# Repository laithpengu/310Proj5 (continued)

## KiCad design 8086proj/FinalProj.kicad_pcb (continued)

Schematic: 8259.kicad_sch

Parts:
C801, C802: .1uF; CP_Elec_3x5.3
J801: Conn_01x04_Male; PinHeader_1x04_P1.00mm_Vertical
R801, R802: 10k; R_0201_0603Metric
SW801: SW_Push; SW_Cherry_MX_1.00u_PCB
U801, U802: 74LS21; DIP-14_W10.16mm
U803: PAL16L8; DIP-20_W7.62mm
U804: 8259; DIP-28_W15.24mm

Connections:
/8086/INTR: U804.17 (INT); also elsewhere on the board
/8254/C2out: U804.19 (IR1); also elsewhere on the board
/8259/8279 IRQ: U804.20 (IR2); also elsewhere on the board
/16550/A0: U803.2 (I2); also elsewhere on the board
/16550/A1: U804.27 (A0); also elsewhere on the board
/16550/A2: U803.3 (I3); also elsewhere on the board
/16550/A3: U803.4 (I4); also elsewhere on the board
/16550/A4: U801.1; also elsewhere on the board
/16550/A5: U801.2; also elsewhere on the board
/16550/A6: U801.4; also elsewhere on the board
/16550/A7: U801.5; also elsewhere on the board
/16550/A8: U801.9; also elsewhere on the board
/16550/A9: U801.10; also elsewhere on the board
/16550/A10: U801.12; also elsewhere on the board
/16550/A11: U801.13; also elsewhere on the board
/16550/A12: U802.9; also elsewhere on the board
/16550/A13: U802.10; also elsewhere on the board
/16550/A14: U802.12; also elsewhere on the board
/16550/A15: U802.13; also elsewhere on the board
/16550/D0: U804.11 (D0); also elsewhere on the board
/16550/D1: U804.10 (D1); also elsewhere on the board
/16550/D2: U804.9 (D2); also elsewhere on the board
/16550/D3: U804.8 (D3); also elsewhere on the board
/16550/D4: U804.7 (D4); also elsewhere on the board
/16550/D5: U804.6 (D5); also elsewhere on the board
/16550/D6: U804.5 (D6); also elsewhere on the board
/16550/D7: U804.4 (D7); also elsewhere on the board
/16550/INTR: U804.21 (IR3); also elsewhere on the board
/16550/M/_IO: U803.1 (I1); also elsewhere on the board
/16550/_RD: U804.3 (~RD); also elsewhere on the board
/16550/_WR: U804.2 (~WR); also elsewhere on the board
unnamed: J801.1, U804.22 (IR4)
unnamed: J801.2, U804.23 (IR5)
unnamed: J801.3, U804.24 (IR6)
unnamed: J801.4, U804.25 (IR7)
unnamed: R801.1, U804.16 (~SP/~EN)
unnamed: R802.1, SW801.1, U804.18 (IR0)
unnamed: U801.6, U803.5 (I5)
unnamed: U801.8, U803.6 (I6)
unnamed: U802.8, U803.7 (I7)
unnamed: U803.19 (IO1), U804.1 (~CS)

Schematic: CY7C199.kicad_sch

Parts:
C501, C502, C503, C504, C505: .1uF; CP_Elec_3x5.3
U501: PAL16L8; DIP-20_W7.62mm
U502, U503, U504, U505: CY7C199; DIP-28_W15.24mm

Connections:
/16550/A0: U502.21 (A0), U503.21 (A0), U504.21 (A0), U505.21 (A0); also elsewhere on the board
/16550/A1: U502.23 (A1), U503.23 (A1), U504.23 (A1), U505.23 (A1); also elsewhere on the board
/16550/A2: U502.24 (A2), U503.24 (A2), U504.24 (A2), U505.24 (A2); also elsewhere on the board
/16550/A3: U502.25 (A3), U503.25 (A3), U504.25 (A3), U505.25 (A3); also elsewhere on the board
/16550/A4: U502.26 (A4), U503.26 (A4), U504.26 (A4), U505.26 (A4); also elsewhere on the board
/16550/A5: U502.1 (A5), U503.1 (A5), U504.1 (A5), U505.1 (A5); also elsewhere on the board
/16550/A6: U502.2 (A6), U503.2 (A6), U504.2 (A6), U505.2 (A6); also elsewhere on the board
/16550/A7: U502.3 (A7), U503.3 (A7), U504.3 (A7), U505.3 (A7); also elsewhere on the board
/16550/A8: U502.4 (A8), U503.4 (A8), U504.4 (A8), U505.4 (A8); also elsewhere on the board
/16550/A9: U502.5 (A9), U503.5 (A9), U504.5 (A9), U505.5 (A9); also elsewhere on the board
/16550/A10: U502.6 (A10), U503.6 (A10), U504.6 (A10), U505.6 (A10); also elsewhere on the board
/16550/A11: U502.7 (A11), U503.7 (A11), U504.7 (A11), U505.7 (A11); also elsewhere on the board
/16550/A12: U502.8 (A12), U503.8 (A12), U504.8 (A12), U505.8 (A12); also elsewhere on the board
/16550/A13: U502.9 (A13), U503.9 (A13), U504.9 (A13), U505.9 (A13); also elsewhere on the board
/16550/A14: U502.10 (A14), U503.10 (A14), U504.10 (A14), U505.10 (A14); also elsewhere on the board
/16550/D0: U502.11 (D0), U504.11 (D0); also elsewhere on the board
/16550/D1: U502.12 (D1), U504.12 (D1); also elsewhere on the board
/16550/D2: U502.13 (D2), U504.13 (D2); also elsewhere on the board
/16550/D3: U502.15 (D3), U504.15 (D3); also elsewhere on the board
/16550/D4: U502.16 (D4), U504.16 (D4); also elsewhere on the board
/16550/D5: U502.17 (D5), U504.17 (D5); also elsewhere on the board
/16550/D6: U502.18 (D6), U504.18 (D6); also elsewhere on the board
/16550/D7: U502.19 (D7), U504.19 (D7); also elsewhere on the board
/16550/D8: U503.11 (D0), U505.11 (D0); also elsewhere on the board
/16550/D9: U503.12 (D1), U505.12 (D1); also elsewhere on the board
/16550/D10: U503.13 (D2), U505.13 (D2); also elsewhere on the board
/16550/D11: U503.15 (D3), U505.15 (D3); also elsewhere on the board
/16550/D12: U503.16 (D4), U505.16 (D4); also elsewhere on the board
/16550/D13: U503.17 (D5), U505.17 (D5); also elsewhere on the board
/16550/D14: U503.18 (D6), U505.18 (D6); also elsewhere on the board
/16550/D15: U503.19 (D7), U505.19 (D7); also elsewhere on the board
/16550/M/_IO: U501.2 (I2); also elsewhere on the board
/16550/_RD: U502.27 (~WE), U503.27 (~WE), U504.27 (~WE), U505.27 (~WE); also elsewhere on the board
/16550/_WR: U502.22 (~OE), U503.22 (~OE), U504.22 (~OE), U505.22 (~OE); also elsewhere on the board
/CY7C199/A16: U501.1 (I1)
/CY7C199/_CE0: U501.19 (IO1), U502.20 (~CE), U503.20 (~CE)
/CY7C199/_CE1: U501.18 (IO2), U504.20 (~CE), U505.20 (~CE)

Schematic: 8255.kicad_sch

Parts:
C601, C602, C603: .1uf; CP_Elec_3x5.3
J601, J602, J603, J604, J605, J606, J607, J608, J609: Conn_01x08_Male; PinHeader_1x08_P1.00mm_Vertical
SW601: SW_DIP_x08; SW_DIP_SPSTx08_Slide_6.7x21.88mm_W6.73mm_P2.54mm_LowProfile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
U601: PAL16L8; DIP-20_W7.62mm
U602, U605, U608: 8255; DIP-40_W15.24mm
U603, U609: 74AUC2G32; DIP-14_W10.16mm
U604: 4011; DIP-14_W10.16mm
U606: 74AHCT04; DIP-14_W10.16mm
U607: 74LVC1G332; DIP-14_W10.16mm

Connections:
/8086/INTR: U606.1, U607.4; also elsewhere on the board
/8255/O5: U601.15 (IO5), U602.6 (~CS)
/8255/O6: U601.14 (IO6), U605.6 (~CS)
/8255/O7: U601.13 (IO7), U608.6 (~CS)
/16550/A0: U601.1 (I1); also elsewhere on the board
/16550/A1: U602.9 (A0), U605.9 (A0), U608.9 (A0); also elsewhere on the board
/16550/A2: U602.8 (A1), U605.8 (A1), U608.8 (A1); also elsewhere on the board
/16550/A3: U601.2 (I2); also elsewhere on the board
/16550/A4: U601.3 (I3); also elsewhere on the board
/16550/A5: U601.4 (I4); also elsewhere on the board
/16550/A6: U601.5 (I5); also elsewhere on the board
/16550/A7: U601.6 (I6); also elsewhere on the board
/16550/A8: U601.7 (I7); also elsewhere on the board
/16550/A9: U601.8 (I8); also elsewhere on the board
/16550/A10: U601.9 (I9); also elsewhere on the board
/16550/A11: U601.11 (I10); also elsewhere on the board
/16550/A12: U601.19 (IO1); also elsewhere on the board
/16550/A13: U601.18 (IO2); also elsewhere on the board
/16550/A14: U601.17 (I03); also elsewhere on the board
/16550/A15: U601.16 (IO4); also elsewhere on the board
/16550/D0: SW601.9, U602.34 (D0), U605.34 (D0), U608.34 (D0); also elsewhere on the board
/16550/D1: SW601.10, U602.33 (D1), U605.33 (D1), U608.33 (D1); also elsewhere on the board
/16550/D2: SW601.11, U602.32 (D2), U605.32 (D2), U608.32 (D2); also elsewhere on the board
/16550/D3: SW601.12, U602.31 (D3), U605.31 (D3), U608.31 (D3); also elsewhere on the board
/16550/D4: SW601.13, U602.30 (D4), U605.30 (D4), U608.30 (D4); also elsewhere on the board
/16550/D5: SW601.14, U602.29 (D5), U605.29 (D5), U608.29 (D5); also elsewhere on the board
/16550/D6: SW601.15, U602.28 (D6), U605.28 (D6), U608.28 (D6); also elsewhere on the board
/16550/D7: SW601.16, U602.27 (D7), U605.27 (D7), U608.27 (D7); also elsewhere on the board
/16550/MR: U602.35 (RESET), U605.35 (RESET), U608.35 (RESET); also elsewhere on the board
/16550/M/_IO: U601.12 (IO8); also elsewhere on the board
/16550/_RD: U602.5 (~RD), U605.5 (~RD), U608.5 (~RD); also elsewhere on the board
/16550/_WR: U602.36 (~WR), U605.36 (~WR), U608.36 (~WR); also elsewhere on the board
unnamed: J601.1, U602.37 (PA7)
unnamed: J601.2, U602.38 (PA6)
unnamed: J601.3, U602.39 (PA5)
unnamed: J601.4, U602.40 (PA4)
unnamed: J601.5, U602.1 (PA3)
unnamed: J601.6, U602.2 (PA2)
unnamed: J601.7, U602.3 (PA1)
unnamed: J601.8, U602.4 (PA0)
unnamed: J602.1, U602.25 (PB7)
unnamed: J602.2, U602.24 (PB6)
unnamed: J602.3, U602.23 (PB5)
unnamed: J602.4, U602.22 (PB4)
unnamed: J602.5, U602.21 (PB3)
unnamed: J602.6, U602.20 (PB2)
unnamed: J602.7, U602.19 (PB1)
unnamed: J602.8, U602.18 (PB0)
unnamed: J603.1, U602.10 (PC7)
unnamed: J603.3, U602.12 (PC5)
unnamed: J603.4, U602.13 (PC4)
unnamed: J603.5, U602.17 (PC3), U603.1
unnamed: J603.7, U602.15 (PC1)
unnamed: J604.1, U605.37 (PA7)
unnamed: J604.2, U605.38 (PA6)
unnamed: J604.3, U605.39 (PA5)
unnamed: J604.4, U605.40 (PA4)
unnamed: J604.5, U605.1 (PA3)
unnamed: J604.6, U605.2 (PA2)
unnamed: J604.7, U605.3 (PA1)
unnamed: J604.8, U605.4 (PA0)
unnamed: J605.1, U605.25 (PB7)
unnamed: J605.2, U605.24 (PB6)
unnamed: J605.3, U605.23 (PB5)
unnamed: J605.4, U605.22 (PB4)
unnamed: J605.5, U605.21 (PB3)
unnamed: J605.6, U605.20 (PB2)
unnamed: J605.7, U605.19 (PB1)
unnamed: J605.8, U605.18 (PB0)
unnamed: J606.1, U605.10 (PC7)
unnamed: J606.3, U605.12 (PC5)
unnamed: J606.4, U605.13 (PC4)
unnamed: J606.5, U603.5, U605.17 (PC3)
unnamed: J606.7, U605.15 (PC1)
unnamed: J606.8, U603.6, U605.14 (PC0)
unnamed: J607.1, U608.37 (PA7)
unnamed: J607.2, U608.38 (PA6)
unnamed: J607.3, U608.39 (PA5)
unnamed: J607.4, U608.40 (PA4)
unnamed: J607.5, U608.1 (PA3)
unnamed: J607.6, U608.2 (PA2)
unnamed: J607.7, U608.3 (PA1)
unnamed: J607.8, U608.4 (PA0)
unnamed: J608.1, U608.25 (PB7)
unnamed: J608.2, U608.24 (PB6)
unnamed: J608.3, U608.23 (PB5)
unnamed: J608.4, U608.22 (PB4)
unnamed: J608.5, U608.21 (PB3)
unnamed: J608.6, U608.20 (PB2)
unnamed: J608.7, U608.19 (PB1)
unnamed: J608.8, U608.18 (PB0)
unnamed: J609.1, U608.10 (PC7)
unnamed: J609.3, U608.12 (PC5)
unnamed: J609.4, U608.13 (PC4)
unnamed: J609.5, U608.17 (PC3), U609.5
unnamed: J609.7, U608.15 (PC1)
unnamed: J609.8, U608.14 (PC0), U609.6
unnamed: SW601.1, SW601.2, SW601.3, SW601.4, SW601.5, SW601.6, SW601.7, SW601.8, U604.3
unnamed: U603.3, U607.1
unnamed: U603.7, U607.3
unnamed: U604.2, U606.2
unnamed: U607.6, U609.3
VCC: U603.8 (VCC), U607.5 (VCC), U609.8 (VCC)

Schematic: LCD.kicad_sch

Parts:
C1201, C1202: C; CP_Elec_3x5.3
DS1201: LCD4x20; LCD-016N002L; Mouser Part Number 763-0420AZFLYBW33V3
R1201: R; R_0201_0603Metric
U1201: PAL16L8; DIP-20_W7.62mm

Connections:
/16550/A0: U1201.1 (I1); also elsewhere on the board
/16550/A1: DS1201.4 (RS); also elsewhere on the board
/16550/A3: U1201.16 (IO4); also elsewhere on the board
/16550/A4: U1201.2 (I2); also elsewhere on the board
/16550/A5: U1201.3 (I3); also elsewhere on the board
/16550/A6: U1201.4 (I4); also elsewhere on the board
/16550/A7: U1201.5 (I5); also elsewhere on the board
/16550/A8: U1201.6 (I6); also elsewhere on the board
/16550/A9: U1201.7 (I7); also elsewhere on the board
/16550/A10: U1201.8 (I8); also elsewhere on the board
/16550/A11: U1201.9 (I9); also elsewhere on the board
/16550/A12: U1201.11 (I10); also elsewhere on the board
/16550/A13: U1201.19 (IO1); also elsewhere on the board
/16550/A14: U1201.18 (IO2); also elsewhere on the board
/16550/A15: U1201.17 (I03); also elsewhere on the board
/16550/D0: DS1201.7 (DB0); also elsewhere on the board
/16550/D1: DS1201.8 (DB1); also elsewhere on the board
/16550/D2: DS1201.9 (DB2); also elsewhere on the board
/16550/D3: DS1201.10 (DB3); also elsewhere on the board
/16550/D4: DS1201.11 (DB4); also elsewhere on the board
/16550/D5: DS1201.12 (DB5); also elsewhere on the board
/16550/D6: DS1201.13 (DB6); also elsewhere on the board
/16550/D7: DS1201.14 (DB7); also elsewhere on the board
/16550/M/_IO: U1201.15 (IO5); also elsewhere on the board
/16550/_RD: DS1201.5 (R/W); also elsewhere on the board
unnamed: DS1201.3 (V0), R1201.2
unnamed: DS1201.6 (E), U1201.12 (IO8)

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
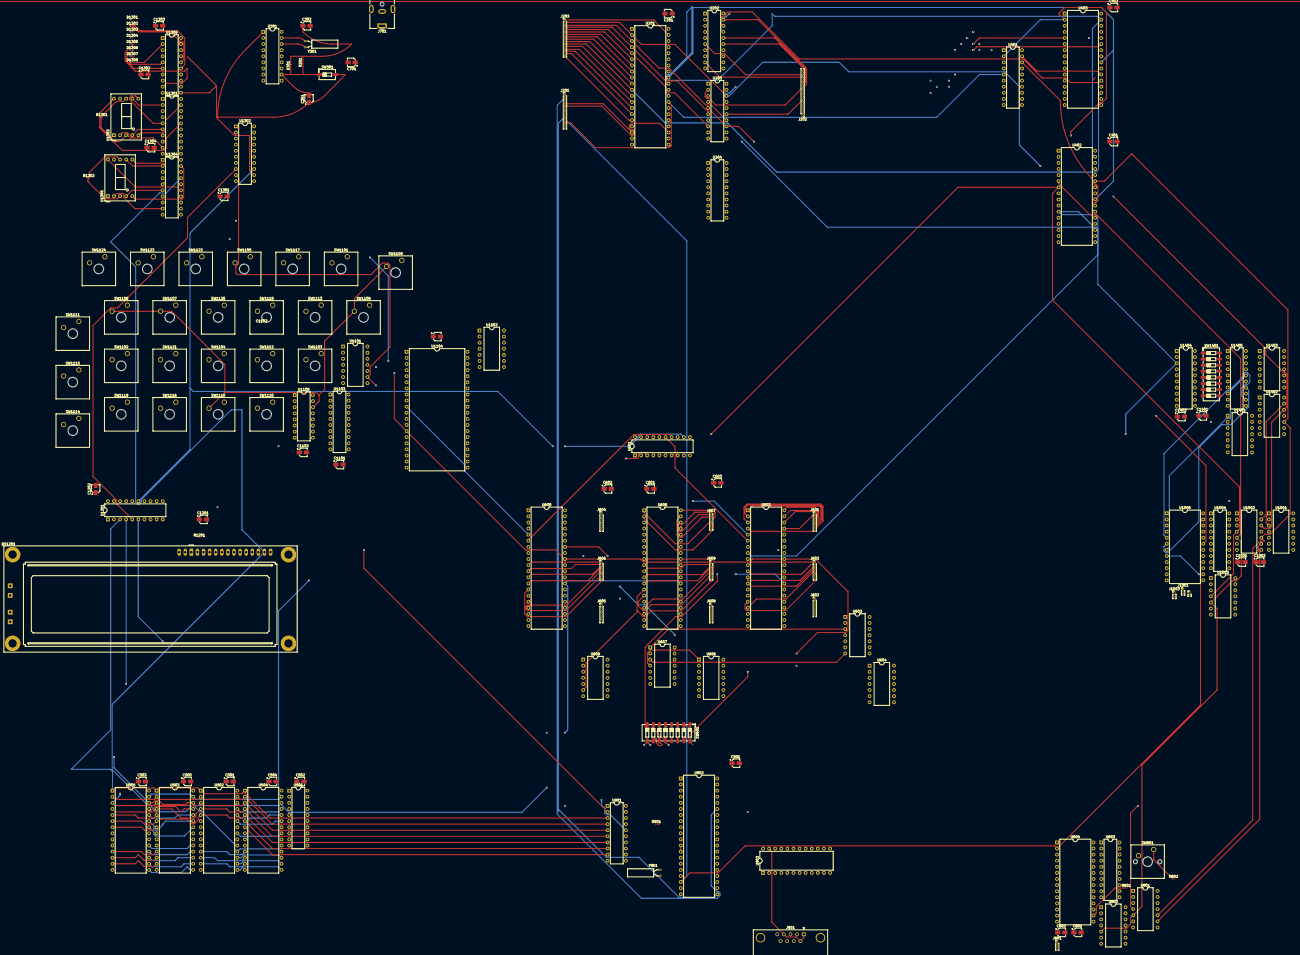
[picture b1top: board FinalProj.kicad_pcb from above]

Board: 10 copper layers, 147 parts (0 on the bottom side), 241 nets.

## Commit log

2022-04-12 Added README file
2022-04-12 kicadFiles
2022-04-15 ethans changes
2022-04-21 clock added
2022-04-25 28F010.kicad_sch
2022-04-25 28F010
2022-04-27 started sram
2022-04-28 finished cy7c199
2022-04-29 28F010 fix
2022-04-29 latch added
2022-04-30 power added
2022-05-02 8255
2022-05-03 8259
2022-05-03 fixes
2022-05-04 16550
2022-05-05 8254 and 8279
2022-05-06 test
2022-05-08 7seg
2022-05-08 74244
2022-05-08 final look
2022-05-09 footprints
2022-05-10 footprint
2022-05-12 pcb update
2022-05-12 pcb edit
2022-05-13 chip size
2022-05-13 pcb edits
